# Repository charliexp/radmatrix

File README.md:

# radmatrix

Smol modular LED matrix, consisting of 3 types of 50x50mm modules:

- LED modules with a 20x20 matrix of 0603 red LEDs
- Driver modules at the end of rows and columns (bottom and right)
- Microcontroller (RP2040) board in the bottom-right corner

This was built as my first "serious" electronics project and its main purpose was to learn electronics a bit better. Some RP2040 embedded knowledge and a blinky lights object are nice side effects.

## Results

TODO: Photos, video, PCB renders

## Design details

The LED matrix and driver module PCB design were optimized for JLCPCB Assembly - i.e. only using parts available in its (LCSC) catalog and strongly preferring Basic parts to avoid paying feeder fees. The LEDs chosen were the cheapest available in JLC's catalog (they work fine btw).

The microcontroller board was optimized for JLC PCBA to a lesser extent -- I used multiple parts that would incur a feeder fee if not for the fact that I hand-soldered them.

The display is capable of:

- 8 bit red color
- 60fps (TODO, 30fps demonstrated)

Additionally, the MCU board can:

- Read multiple "videos" (specially encoded for this firmware) from an SD card
- Pipe in 8-bit 44kHz audio
- Transmit and receive CAN messages

## v2

Now that I've leraned from my mistakes, here's what I would do if I were to build a v2 of this display (I probably won't):

- Use square, preferably RGB LED "pixels"
- Fit them in a grid of **standard** spacing (i.e. 1, 1.27, 2, or 2.54mm)
- Put pixels edge to edge
  - Current design simplfiied connections and JLC assembly, but it's ugly
- Use a black PCB for the LED matrix for increased contrast
- Move driver modules from column/row ends to the backs of LED modules
  - The current design is kinda neat, but it doesn't scale, as with each additional row of modules, the perceptual brightness of LEDs goes down
- A 2mm-spacing 32x32 standard module seems reasonable
- Connection between LED module and driver module would be done by placing 1x16 SMD pin headers alongside corners (split in half, say, bottom-left and top-right for rows, and likewise for columns to allow edge-to-edge clearance)
  - Possibly some additional pin headers for added stability, maybe some solderable nuts - some mechanical connection between modules would be nice
- Driver modules
  - Would consider constant-current drivers, although resistor-based approach seems to work fine and appeared cheaper
  - If resistor-based approach is still used, I would consider a buck converter for creating a variable LED power supply
  - Would consider not skipping any of the shift register stages as that makes programming more annoying, and in this approach, it shouldn't make layout too difficult
  - Fix v1 bugs of course
  - Would consider faster shift registers. Perhaps 74HCT (5V supply to '595 gives best performance, and HCT can handle 3v3 input), or LV*
  - Would consider a decoder instead of shift registers for selecting rows. The current method is risky in that if programming is not done correctly, multiple LED rows could be lighting up at the same time (with one resistor for multiple LEDs), overstressing them. It's likely that current approach is cheaper and requires fewer signal lines though
- Driving the display
  - Each LED/driver module would have a separate connection to the MCU board - sharing row selection, OE, SRCLK, RCLK, lines, but each having its own SER line
  - With PIO, this would have minimal impact on driving performance, and RP2040 IO counts would likely allow for 16-20 module to be connected to a single MCU board
  - This could in principle be extended further with multiple MCU boards talking to a master
  - The display would become /32, so would be brighter and that would not depend on its height
  - Each driver module should have a buffer before/after it to improve the signal

Note that while most people do projects like this with an FPGA, in my opinion the RP2040, thanks to PIO, is more than capable enough for this job at a better price, and can do other stuff in addition to just driving the display. The main downside vs an FPGA is limited IO (30 pins), which limits how big of a display can be driven. With the design above, likely ~20kpx (though this could be optimized further)

Noting the above so I don't forget or in case someone else wants to take this project further. To me, this project has fulfilled its educational goal, and making large LED displays this way is impractical given that you can get HUB75 modules for less than just the LED cost off LCSC.

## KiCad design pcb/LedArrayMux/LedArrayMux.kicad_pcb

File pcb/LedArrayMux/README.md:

# LED Multiplexer

50x50mm module for driving rows and columns of LED Matrix modules

## Revisions

### Rev A

Manufactured 2024-04-06, delivered 2024-04-13.

Errata:

1. PMOS gates are pulled up to VLED (5V), while the shift register is powered from 3V3 and signals above VCC are not allowed. Ouch!
   - NMOS gates (i.e. row drivers) are not affected
   - This is not easily fixable on the board itself
   - It doesn't appear that 74HC595 dies immediately because of this, and the 10k resistor would limit worst-case scenario current to 0.5mA, but probably bad idea to ignore this altogether
   - It's possible to set VCC to 5V, and add level shifting on signal lines
   - Alternatively, the shift register could be replaced with 74HCT595 so that 3V3 signals register as logic high at 5V VCC

### Rev B

Ordered for manufacturing 2024-11-04 (est.), delivered TBD

Minor layout tweaks + added more decoupling capacitance. The major bugs are not fixed, as this rev is for a display that has it worked around.

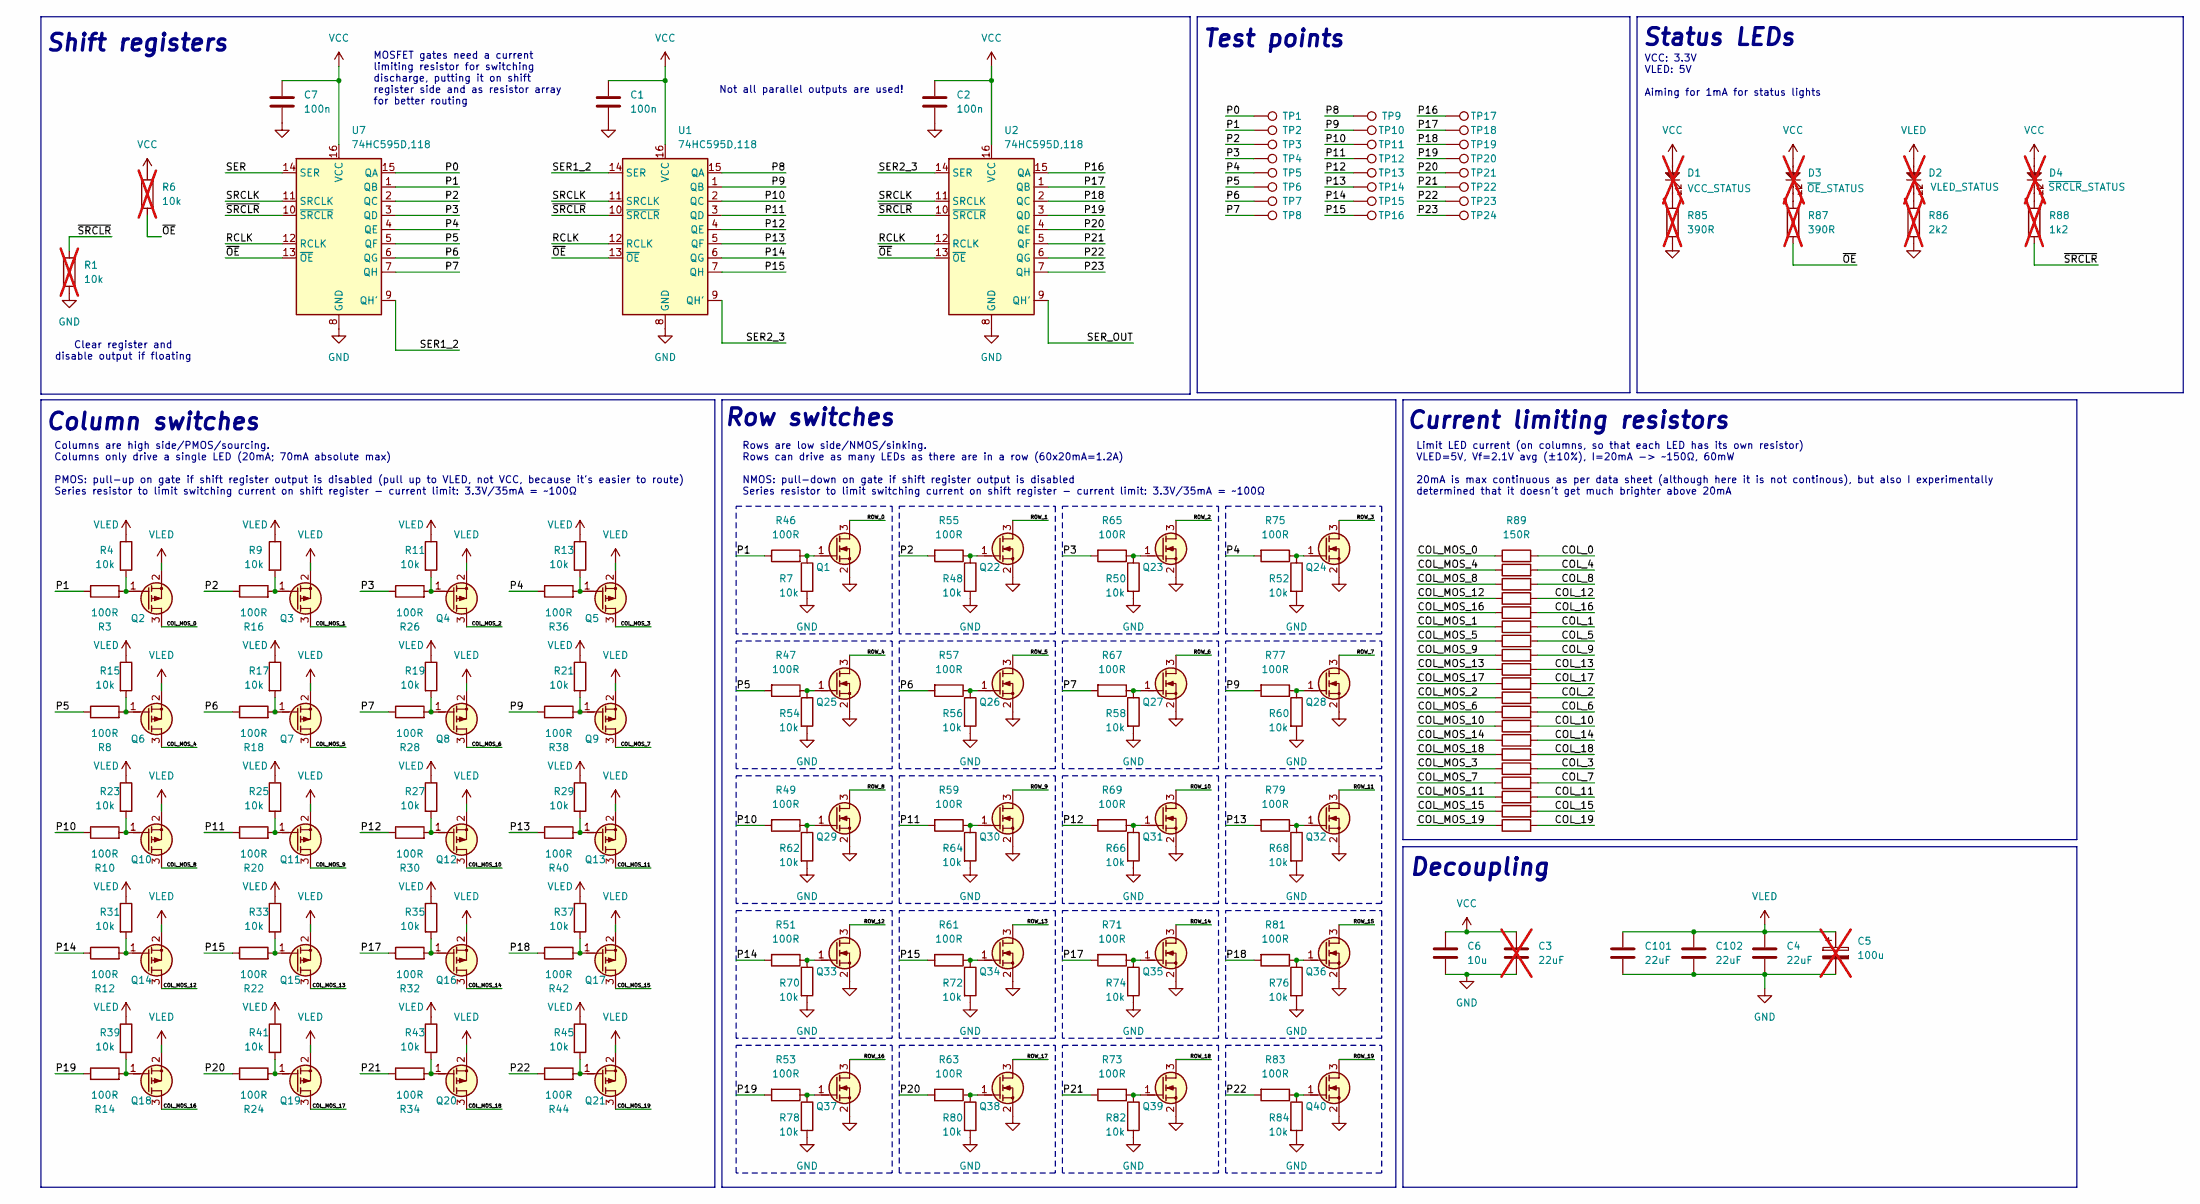
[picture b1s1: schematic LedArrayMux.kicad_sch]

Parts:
C1, C2, C7: 100n; R_0402_1005Metric; LCSC C307331
C3: 22uF; C_1206_3216Metric; LCSC C12891; not fitted
C4, C101, C102: 22uF; C_1206_3216Metric; LCSC C12891
C5: 100u; CP_EIA-3528-15_AVX-H; LCSC C16133; not fitted
C6: 10u; C_0603_1608Metric; LCSC C96446
D1, D2, D3: KT-0805G; LED_0805_2012Metric; LCSC C2297; not fitted
D4: KT-0805Y; LED_0805_2012Metric; LCSC C2296; not fitted
Q1, Q22, Q23, Q24, Q25, Q26, Q27, Q28, Q29, Q30, Q31, Q32, Q33, Q34, Q35, Q36, Q37, Q38, Q39, Q40: HL2304; SOT-23; LCSC C7420346
Q2, Q3, Q4, Q5, Q6, Q7, Q8, Q9, Q10, Q11, Q12, Q13, Q14, Q15, Q16, Q17, Q18, Q19, Q20, Q21: HL2301A; SOT-23; LCSC C7420344
R1, R6: 10k; R_0402_1005Metric; LCSC C25744; not fitted
R3, R8, R10, R12, R14, R16, R18, R20, R22, R24, R26, R28, R30, R32, R34, R36, R38, R40, R42, R44, R46, R47, R49, R51, R53, R55, R57, R59, R61, R63, R65, R67, R69, R71, R73, R75, R77, R79, R81, R83: 100R; R_0402_1005Metric
R4, R7, R9, R11, R13, R15, R17, R19, R21, R23, R25, R27, R29, R31, R33, R35, R37, R39, R41, R43, R45, R48, R50, R52, R54, R56, R58, R60, R62, R64, R66, R68, R70, R72, R74, R76, R78, R80, R82, R84: 10k; R_0402_1005Metric; LCSC C25744
R85, R87: 390R; R_0603_1608Metric; not fitted
R86: 2k2; R_0603_1608Metric; not fitted
R88: 1k2; R_0603_1608Metric; not fitted
R89, R90, R91, R92, R93, R94, R95, R96, R97, R98, R99, R100, R101, R102, R103, R104, R105, R106, R107, R108: 150R; R_0805_2012Metric
TP1, TP2, TP3, TP4, TP5, TP6, TP7, TP8, TP9, TP10, TP11, TP12, TP13, TP14, TP15, TP16, TP17, TP18, TP19, TP20, TP21, TP22, TP23, TP24: TestPoint; TestPoint_Pad_D1.0mm
U1, U2, U7: 74HC595D,118; SO-16_3.9x9.9mm_P1.27mm; LCSC C5947

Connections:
/COL_0: R89.2
/COL_1: R94.2
/COL_2: R99.2
/COL_3: R104.2
/COL_4: R90.2
/COL_5: R95.2
/COL_6: R100.2
/COL_7: R105.2
/COL_8: R91.2
/COL_9: R96.2
/COL_10: R101.2
/COL_11: R106.2
/COL_12: R92.2
/COL_13: R97.2
/COL_14: R102.2
/COL_15: R107.2
/COL_16: R93.2
/COL_17: R98.2
/COL_18: R103.2
/COL_19: R108.2
/COL_MOS_0: Q2.3 (D), R89.1
/COL_MOS_1: Q3.3 (D), R94.1
/COL_MOS_2: Q4.3 (D), R99.1
/COL_MOS_3: Q5.3 (D), R104.1
/COL_MOS_4: Q6.3 (D), R90.1
/COL_MOS_5: Q7.3 (D), R95.1
/COL_MOS_6: Q8.3 (D), R100.1
/COL_MOS_7: Q9.3 (D), R105.1
/COL_MOS_8: Q10.3 (D), R91.1
/COL_MOS_9: Q11.3 (D), R96.1
/COL_MOS_10: Q12.3 (D), R101.1
/COL_MOS_11: Q13.3 (D), R106.1
/COL_MOS_12: Q14.3 (D), R92.1
/COL_MOS_13: Q15.3 (D), R97.1
/COL_MOS_14: Q16.3 (D), R102.1
/COL_MOS_15: Q17.3 (D), R107.1
/COL_MOS_16: Q18.3 (D), R93.1
/COL_MOS_17: Q19.3 (D), R98.1
/COL_MOS_18: Q20.3 (D), R103.1
/COL_MOS_19: Q21.3 (D), R108.1
/P0: TP1.1, U7.15 (QA)
/P1: R3.1, R46.1, TP2.1, U7.1 (QB)
/P2: R16.1, R55.2, TP3.1, U7.2 (QC)
/P3: R26.1, R65.2, TP4.1, U7.3 (QD)
/P4: R36.1, R75.2, TP5.1, U7.4 (QE)
/P5: R8.1, R47.2, TP6.1, U7.5 (QF)
/P6: R18.1, R57.2, TP7.1, U7.6 (QG)
/P7: R28.1, R67.2, TP8.1, U7.7 (QH)
/P8: TP9.1, U1.15 (QA)
/P9: R38.1, R77.2, TP10.1, U1.1 (QB)
/P10: R10.1, R49.2, TP11.1, U1.2 (QC)
/P11: R20.1, R59.2, TP12.1, U1.3 (QD)
/P12: R30.1, R69.2, TP13.1, U1.4 (QE)
/P13: R40.1, R79.2, TP14.1, U1.5 (QF)
/P14: R12.1, R51.2, TP15.1, U1.6 (QG)
/P15: R22.1, R61.2, TP16.1, U1.7 (QH)
/P16: TP17.1, U2.15 (QA)
/P17: R32.1, R71.2, TP18.1, U2.1 (QB)
/P18: R42.1, R81.2, TP19.1, U2.2 (QC)
/P19: R14.1, R53.2, TP20.1, U2.3 (QD)
/P20: R24.1, R63.2, TP21.1, U2.4 (QE)
/P21: R34.1, R73.2, TP22.1, U2.5 (QF)
/P22: R44.1, R83.2, TP23.1, U2.6 (QG)
/P23: TP24.1, U2.7 (QH)
/RCLK: U1.12 (RCLK), U2.12 (RCLK), U7.12 (RCLK)
/ROW_0: Q1.3 (D)
/ROW_1: Q22.3 (D)
/ROW_2: Q23.3 (D)
/ROW_3: Q24.3 (D)
/ROW_4: Q25.3 (D)
/ROW_5: Q26.3 (D)
/ROW_6: Q27.3 (D)
/ROW_7: Q28.3 (D)
/ROW_8: Q29.3 (D)
/ROW_9: Q30.3 (D)
/ROW_10: Q31.3 (D)
/ROW_11: Q32.3 (D)
/ROW_12: Q33.3 (D)
/ROW_13: Q34.3 (D)
/ROW_14: Q35.3 (D)
/ROW_15: Q36.3 (D)
/ROW_16: Q37.3 (D)
/ROW_17: Q38.3 (D)
/ROW_18: Q39.3 (D)
/ROW_19: Q40.3 (D)
/SER: U7.14 (SER)
/SER1_2: U1.14 (SER), U7.9 (QH')
/SER2_3: U1.9 (QH'), U2.14 (SER)
/SER_OUT: U2.9 (QH')
/SRCLK: U1.11 (SRCLK), U2.11 (SRCLK), U7.11 (SRCLK)
/~OE: R6.2, R87.2, U1.13 (~OE), U2.13 (~OE), U7.13 (~OE)
/~SRCLR: R1.1, R88.2, U1.10 (~SRCLR), U2.10 (~SRCLR), U7.10 (~SRCLR)
GND: C1.2, C2.2, C3.2, C4.2, C5.2, C6.2, C7.2, C101.2, C102.2, Q1.2 (S), Q22.2 (S), Q23.2 (S), Q24.2 (S), Q25.2 (S), Q26.2 (S), Q27.2 (S), Q28.2 (S), Q29.2 (S), Q30.2 (S), Q31.2 (S), Q32.2 (S), Q33.2 (S), Q34.2 (S), Q35.2 (S), Q36.2 (S), Q37.2 (S), Q38.2 (S), Q39.2 (S), Q40.2 (S), R1.2, R7.2, R48.2, R50.2, R52.2, R54.2, R56.2, R58.2, R60.2, R62.2, R64.2, R66.2, R68.2, R70.2, R72.2, R74.2, R76.2, R78.2, R80.2, R82.2, R84.2, R85.2, R86.2, U1.8 (GND), U2.8 (GND), U7.8 (GND)
unnamed: D1.1, R85.1
unnamed: D2.1, R86.1
unnamed: D3.1, R87.1
unnamed: D4.1, R88.1
unnamed: Q1.1 (G), R7.1, R46.2
unnamed: Q2.1 (G), R3.2, R4.2
unnamed: Q3.1 (G), R9.2, R16.2
unnamed: Q4.1 (G), R11.2, R26.2
unnamed: Q5.1 (G), R13.2, R36.2
unnamed: Q6.1 (G), R8.2, R15.2
unnamed: Q7.1 (G), R17.2, R18.2
unnamed: Q8.1 (G), R19.2, R28.2
unnamed: Q9.1 (G), R21.2, R38.2
unnamed: Q10.1 (G), R10.2, R23.2
unnamed: Q11.1 (G), R20.2, R25.2
unnamed: Q12.1 (G), R27.2, R30.2
unnamed: Q13.1 (G), R29.2, R40.2
unnamed: Q14.1 (G), R12.2, R31.2
unnamed: Q15.1 (G), R22.2, R33.2
unnamed: Q16.1 (G), R32.2, R35.2
unnamed: Q17.1 (G), R37.2, R42.2
unnamed: Q18.1 (G), R14.2, R39.2
unnamed: Q19.1 (G), R24.2, R41.2
unnamed: Q20.1 (G), R34.2, R43.2
unnamed: Q21.1 (G), R44.2, R45.2
unnamed: Q22.1 (G), R48.1, R55.1
unnamed: Q23.1 (G), R50.1, R65.1
unnamed: Q24.1 (G), R52.1, R75.1
unnamed: Q25.1 (G), R47.1, R54.1
unnamed: Q26.1 (G), R56.1, R57.1
unnamed: Q27.1 (G), R58.1, R67.1
unnamed: Q28.1 (G), R60.1, R77.1
unnamed: Q29.1 (G), R49.1, R62.1
unnamed: Q30.1 (G), R59.1, R64.1
unnamed: Q31.1 (G), R66.1, R69.1
unnamed: Q32.1 (G), R68.1, R79.1
unnamed: Q33.1 (G), R51.1, R70.1
unnamed: Q34.1 (G), R61.1, R72.1
unnamed: Q35.1 (G), R71.1, R74.1
unnamed: Q36.1 (G), R76.1, R81.1
unnamed: Q37.1 (G), R53.1, R78.1
unnamed: Q38.1 (G), R63.1, R80.1
unnamed: Q39.1 (G), R73.1, R82.1
unnamed: Q40.1 (G), R83.1, R84.1
VCC: C1.1, C2.1, C3.1, C6.1, C7.1, D1.2, D3.2, D4.2, R6.1, U1.16 (VCC), U2.16 (VCC), U7.16 (VCC)
VLED: C4.1, C5.1, C101.1, C102.1, D2.2, Q2.2 (S), Q3.2 (S), Q4.2 (S), Q5.2 (S), Q6.2 (S), Q7.2 (S), Q8.2 (S), Q9.2 (S), Q10.2 (S), Q11.2 (S), Q12.2 (S), Q13.2 (S), Q14.2 (S), Q15.2 (S), Q16.2 (S), Q17.2 (S), Q18.2 (S), Q19.2 (S), Q20.2 (S), Q21.2 (S), R4.1, R9.1, R11.1, R13.1, R15.1, R17.1, R19.1, R21.1, R23.1, R25.1, R27.1, R29.1, R31.1, R33.1, R35.1, R37.1, R39.1, R41.1, R43.1, R45.1

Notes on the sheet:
Rows are low side/NMOS/sinking. Rows can drive as many LEDs as there are in a row (60x20mA=1.2A) NMOS: pull-down on gate if shift register output is disabled Series resistor to limit switching current on shift register - current limit: 3.3V/35mA = ~100Ω
Columns are high side/PMOS/sourcing. Columns only drive a single LED (20mA; 70mA absolute max) PMOS: pull-up on gate if shift register output is disabled (pull up to VLED, not VCC, because it's easier to route) Series resistor to limit switching current on shift register - current limit: 3.3V/35mA 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
Limit LED current (on columns, so that each LED has its own resistor) VLED=5V, Vf=2.1V avg (±10%), I=20mA -> ~150Ω, 60mW 20mA is max continuous as per data sheet (although here it is not continous), but also I experimentally determined that it doesn't get much brighter above 20mA
MOSFET gates need a current limiting resistor for switching discharge, putting it on shift register side and as resistor array for better routing
Not all parallel outputs are used!
Test points
Shift registers
Row switches
Status LEDs
Decoupling
VCC: 3.3V VLED: 5V Aiming for 1mA for status lights
Current limiting resistors
Column switches
Clear register and disable output if floating

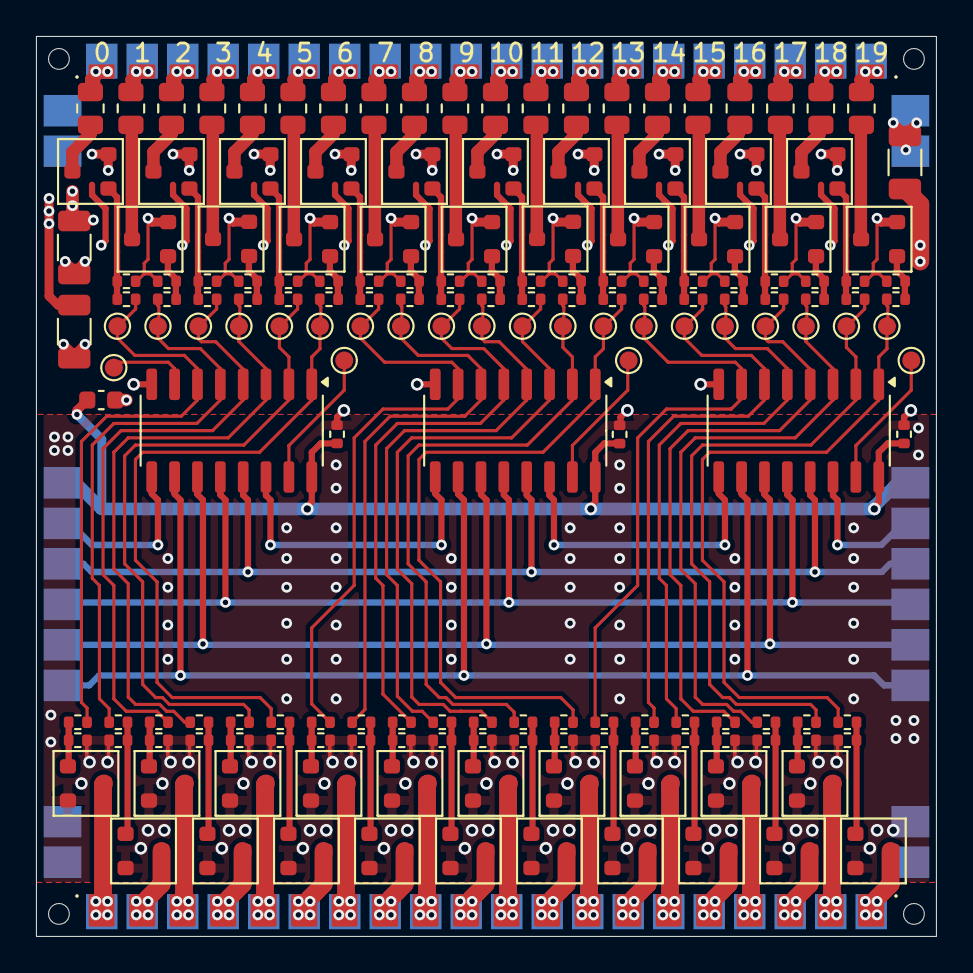
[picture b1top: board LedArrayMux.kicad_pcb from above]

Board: 2 copper layers, 50.0 x 50.0 mm, 174 parts (0 on the bottom side), 93 nets.

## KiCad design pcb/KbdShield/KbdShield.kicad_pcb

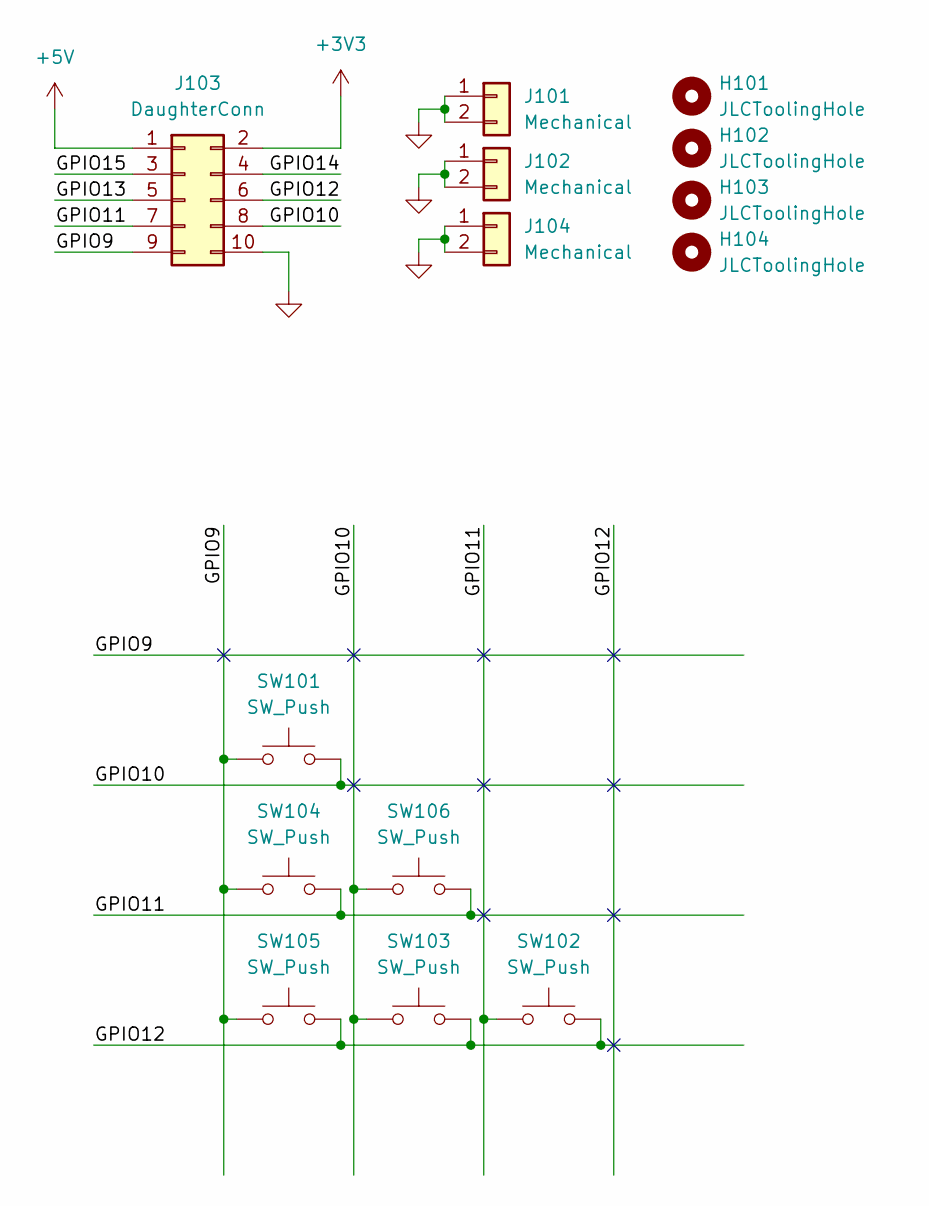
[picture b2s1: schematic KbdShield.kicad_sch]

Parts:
H101, H102, H103, H104: JLCToolingHole; jlcpcb-tooling-hole
J101, J102, J104: Mechanical; PinHeader_1x02_P2.54mm_Vertical
J103: DaughterConn; PinSocket_2x05_P2.54mm_Vertical
SW101, SW102, SW103, SW104, SW105, SW106: SW_Push; SW_Push_1P1T_NO_CK_KSC6xxJ

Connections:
+3V3: J103.2
+5V: J103.1
/GPIO9: J103.9, SW101.1, SW104.1, SW105.1
/GPIO10: J103.8, SW101.2, SW103.1, SW106.1
/GPIO11: J103.7, SW102.1, SW104.2, SW106.2
/GPIO12: J103.6, SW102.2, SW103.2, SW105.2
/GPIO13: J103.5
/GPIO14: J103.4
/GPIO15: J103.3
GND: J101.1, J101.2, J102.1, J102.2, J103.10, J104.1, J104.2

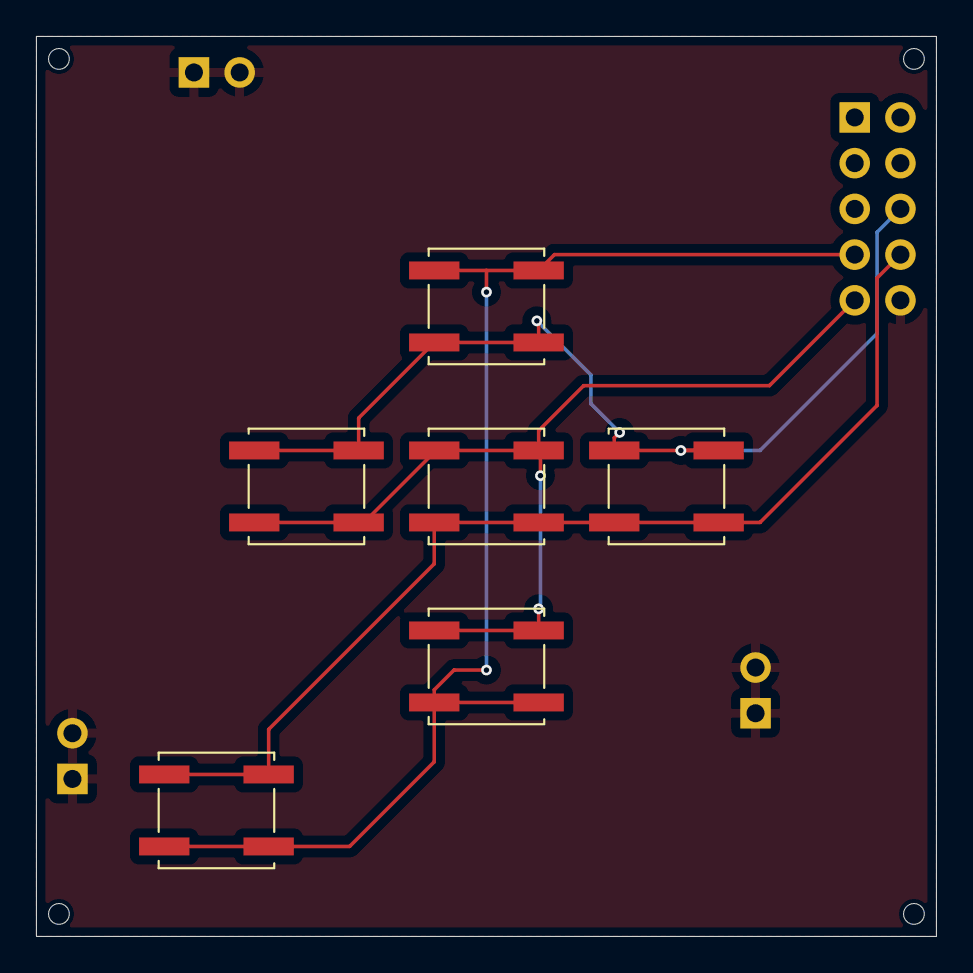
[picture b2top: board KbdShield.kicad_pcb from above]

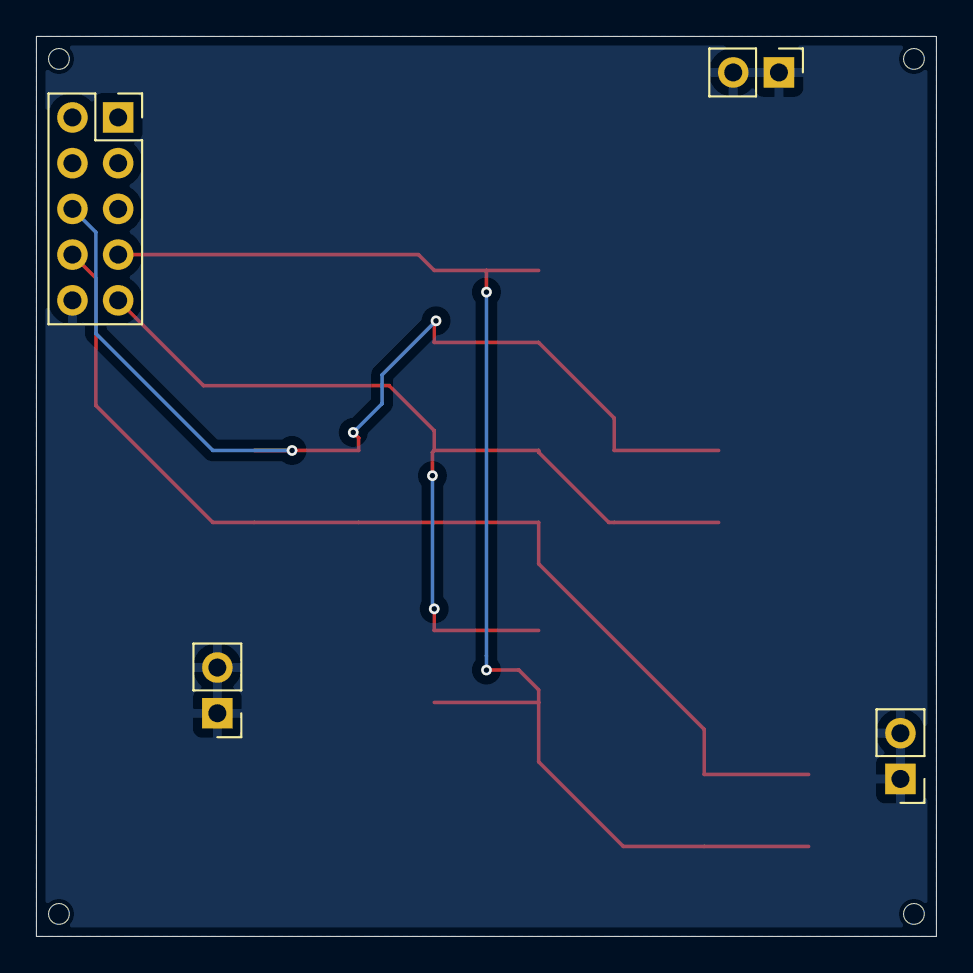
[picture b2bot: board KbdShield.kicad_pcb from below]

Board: 2 copper layers, 50.0 x 50.0 mm, 14 parts (4 on the bottom side), 5 nets.

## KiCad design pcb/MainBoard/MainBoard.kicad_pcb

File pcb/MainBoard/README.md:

# Main Board

50x50mm microcontroller module, driving LedArrayMux modules. Contains an RP2040 microcontroller, a CAN transceiver, PWM audio output, current sensing, and level shifters to work around LedArrayMux bugs.

## Revisions

### Rev A

Errata:

1. Level shifters are too slow to be useful
  - Workaround: decrease pullup values to obnoxiously low ones (100-180Ω); do not use level shifters; increase PIO delays until functional
2. CAN receive signal is not level shifted, which exposes RP2040 to a 5V signal
  - Workaround: Do nothing; replace with a 3v3 CAN transceiver
3. The 431 shunt voltage reference does not work correctly
  - Workaround: use main 3v3 regulator for vref
4. PWM audio signal filter is suspected to be responsible for poor quality audio

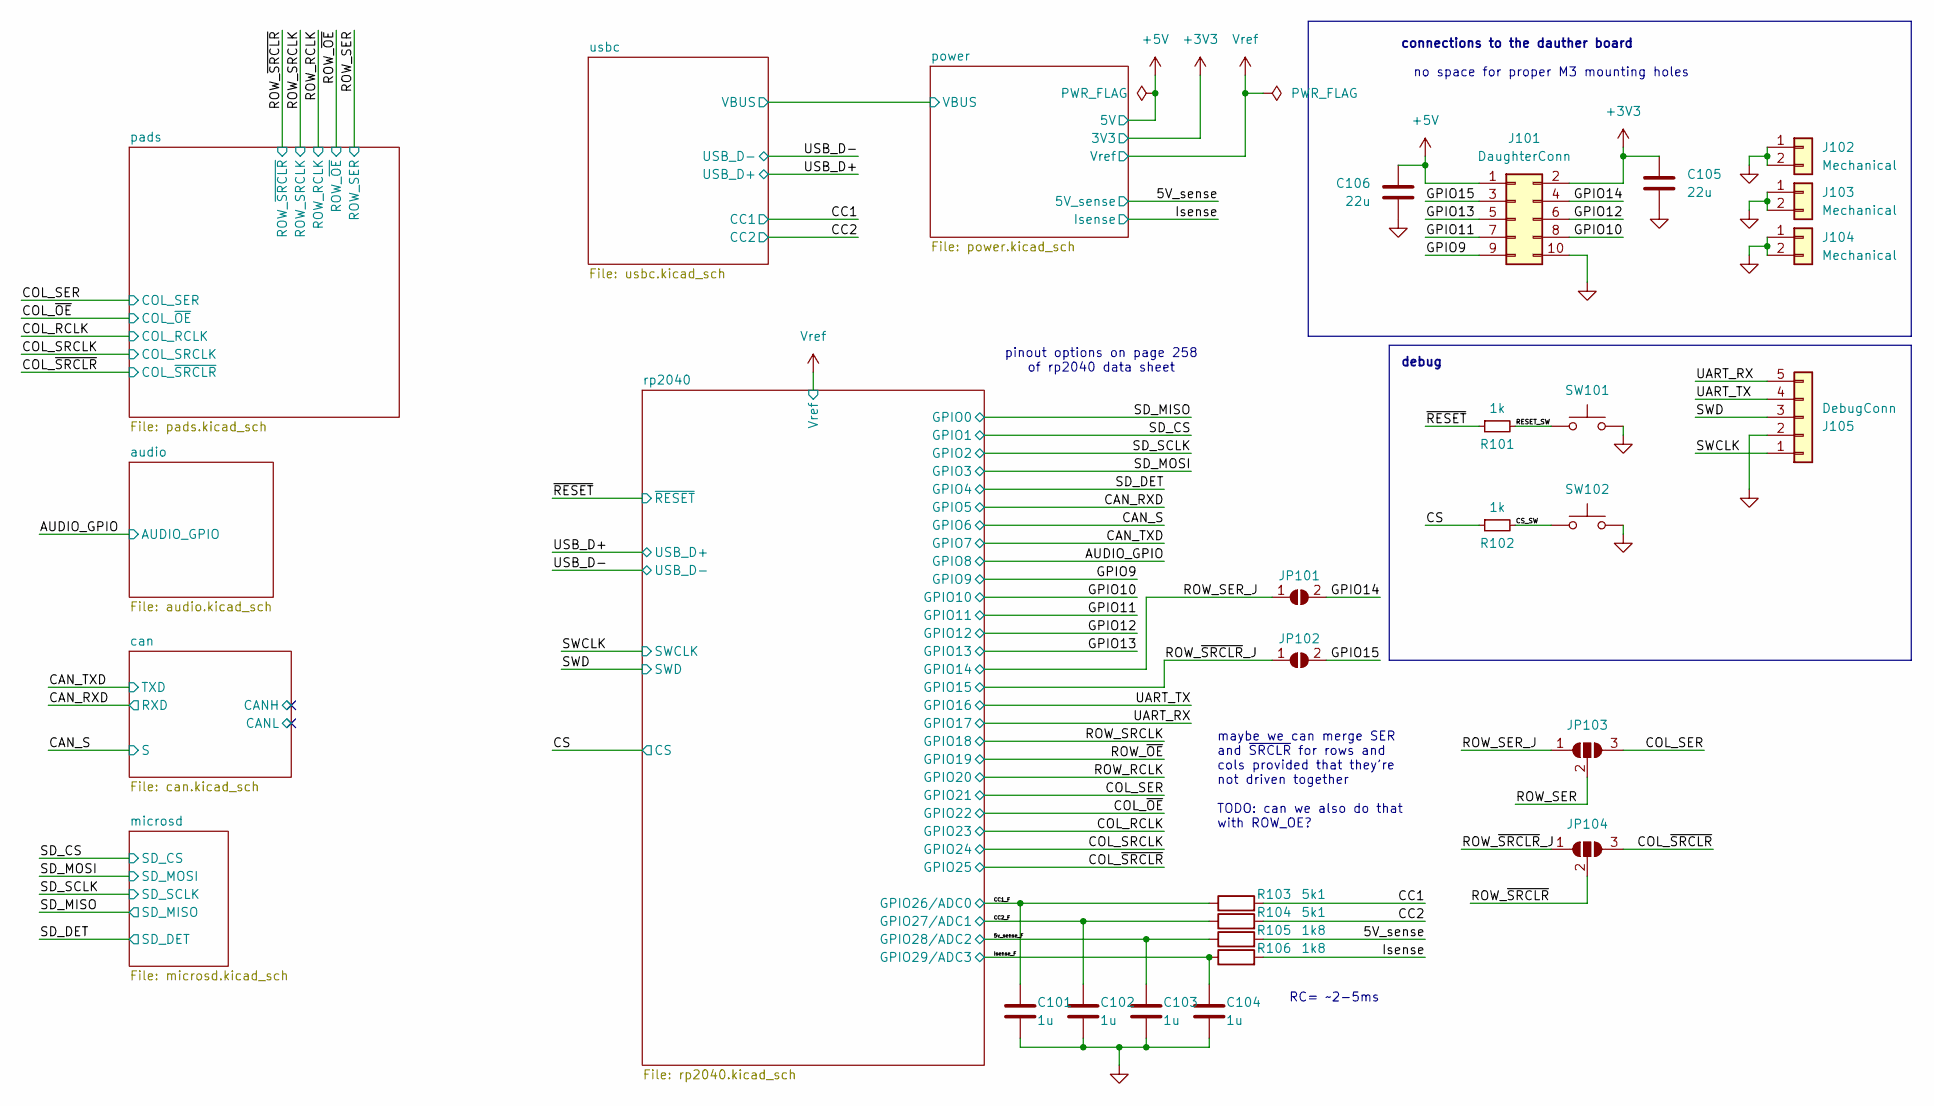
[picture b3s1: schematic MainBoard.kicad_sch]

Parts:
C101, C102, C103, C104: 1u; C_0402_1005Metric; LCSC C52923
C105, C106: 22u; C_0805_2012Metric; LCSC C45783
J101: DaughterConn; PinHeader_2x05_P2.54mm_Vertical
J102, J103, J104: Mechanical; PinHeader_1x02_P2.54mm_Vertical
J105: DebugConn; PinSocket_1x05_P2.54mm_Horizontal
JP101, JP102: SolderJumper_2_Open; SolderJumper-2_Open_RoundedPad_Smol
JP103, JP104: SolderJumper_3_Open; SolderJumper-3_Open_RoundedPad_Smol
R101, R102: 1k; R_0402_1005Metric; LCSC C11702
R103, R104: 5k1; R_0402_1005Metric; LCSC C25905
R105, R106: 1k8; R_0603_1608Metric; LCSC C4177
SW101, SW102: SW; HY-C-03

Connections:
+3V3: C105.1, J101.2; also elsewhere on the board
+5V: C106.1, J101.1; also elsewhere on the board
/5V_sense: R105.2; also elsewhere on the board
/5v_sense_F: C103.1, R105.1; also elsewhere on the board
/CC1: R103.2; also elsewhere on the board
/CC1_F: C101.1, R103.1; also elsewhere on the board
/CC2: R104.2; also elsewhere on the board
/CC2_F: C102.1, R104.1; also elsewhere on the board
/COL_SER: JP103.3 (B); also elsewhere on the board
/COL_~SRCLR: JP104.3 (B); also elsewhere on the board
/CS: R102.1; also elsewhere on the board
/CS_SW: R102.2, SW102.2
/GPIO9: J101.9; also elsewhere on the board
/GPIO10: J101.8; also elsewhere on the board
/GPIO11: J101.7; also elsewhere on the board
/GPIO12: J101.6; also elsewhere on the board
/GPIO13: J101.5; also elsewhere on the board
/GPIO14: J101.4, JP101.2 (B)
/GPIO15: J101.3, JP102.2 (B)
/Isense: R106.2; also elsewhere on the board
/Isense_F: C104.1, R106.1; also elsewhere on the board
/RESET_SW: R101.2, SW101.2
/ROW_SER: JP103.2 (C); also elsewhere on the board
/ROW_SER_J: JP101.1 (A), JP103.1 (A); also elsewhere on the board
/ROW_~SRCLR: JP104.2 (C); also elsewhere on the board
/ROW_~SRCLR_J: JP102.1 (A), JP104.1 (A); also elsewhere on the board
/SWCLK: J105.1; also elsewhere on the board
/SWD: J105.3; also elsewhere on the board
/UART_RX: J105.5; also elsewhere on the board
/UART_TX: J105.4; also elsewhere on the board
/~RESET: R101.1; also elsewhere on the board
GND: C101.2, C102.2, C103.2, C104.2, C105.2, C106.2, J101.10, J102.1, J102.2, J103.1, J103.2, J104.1, J104.2, J105.2, SW101.1, SW102.1; also elsewhere on the board

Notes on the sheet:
RC= ~2-5ms
maybe we can merge SER and ~{SRCLR} for rows and cols provided that they're not driven together TODO: can we also do that with ROW_OE?
pinout options on page 258 of rp2040 data sheet
connections to the dauther board
no space for proper M3 mounting holes
debug

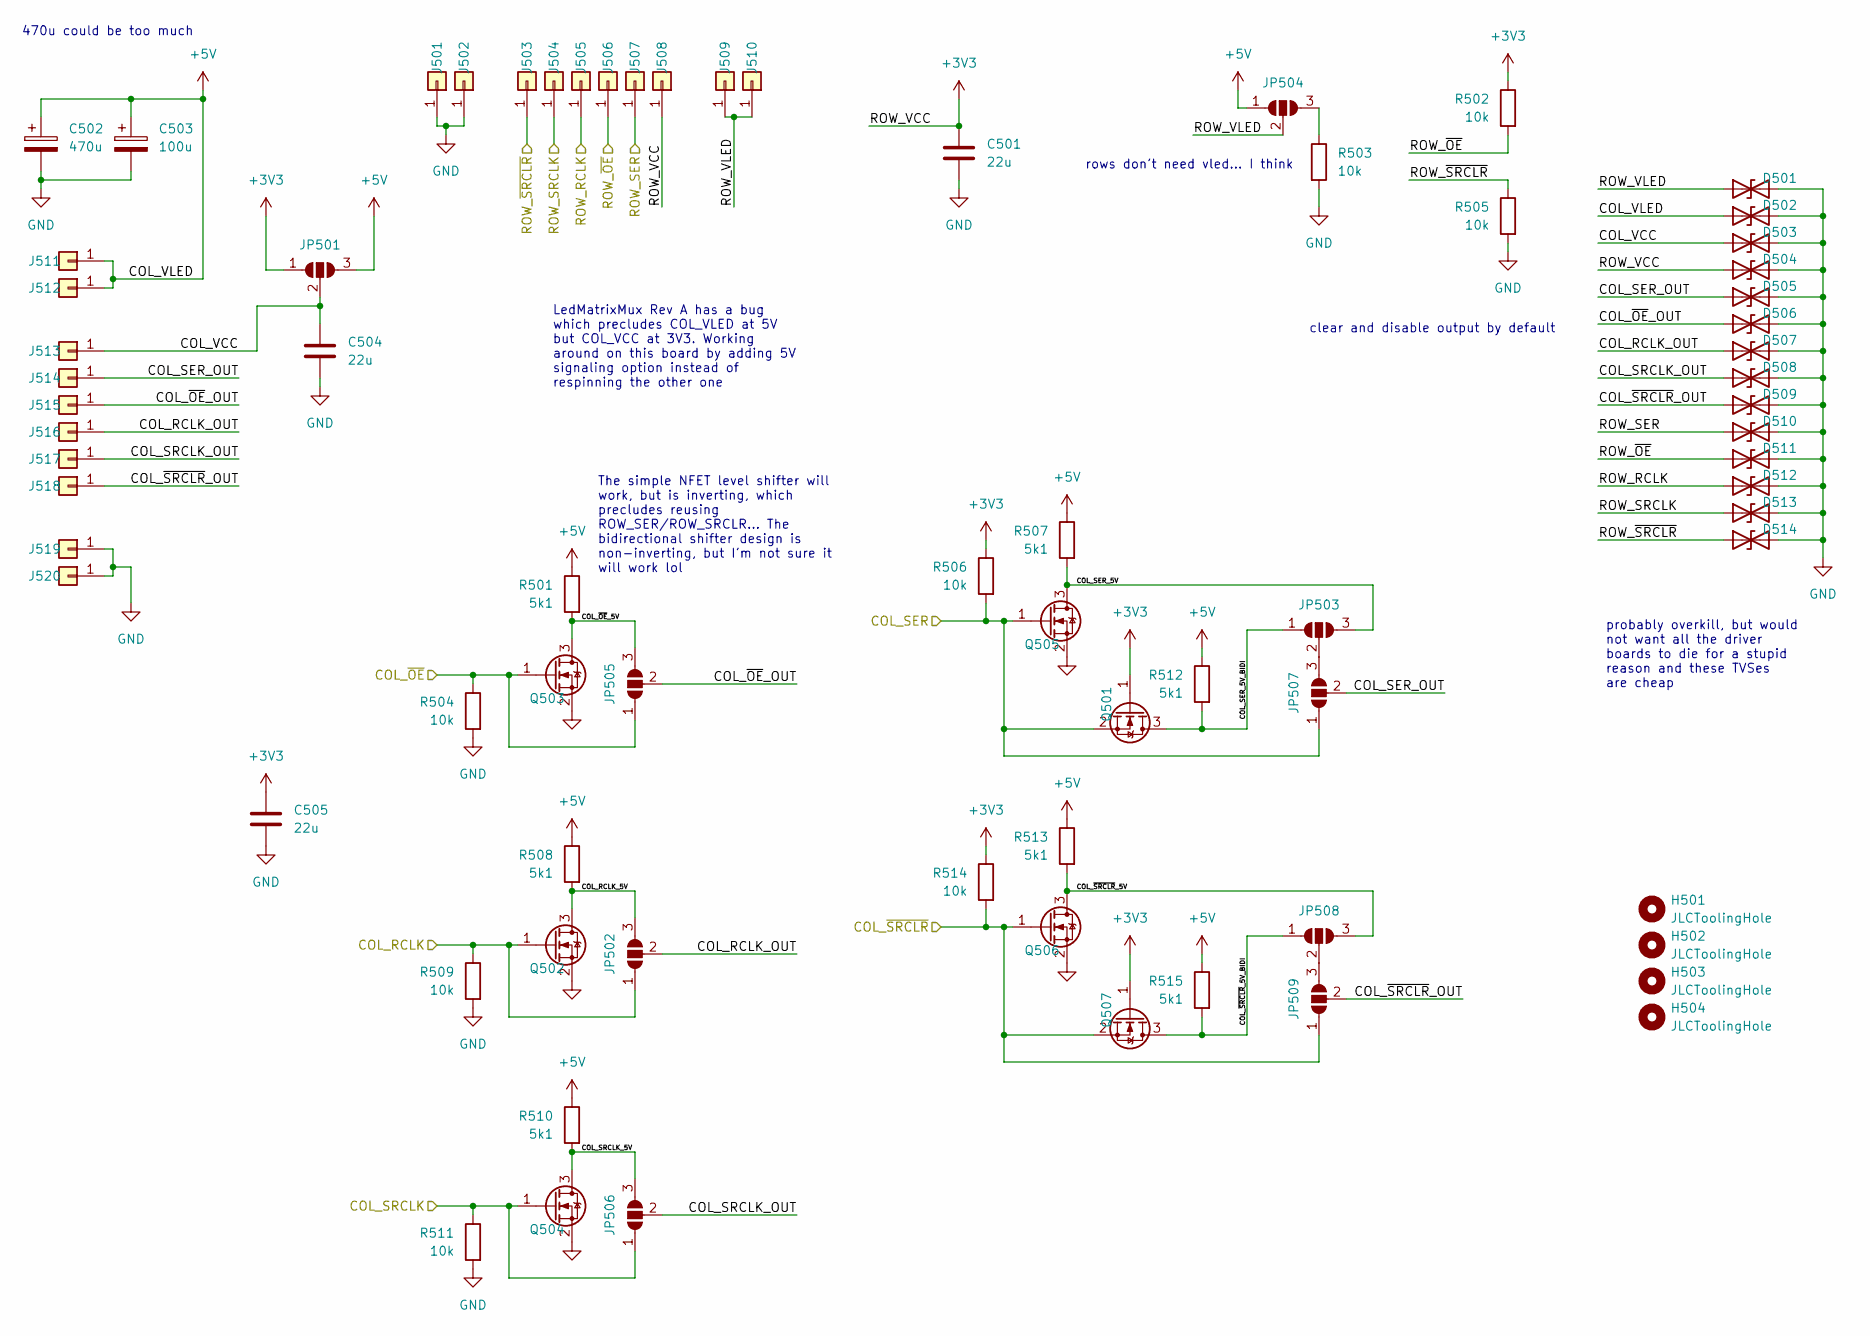
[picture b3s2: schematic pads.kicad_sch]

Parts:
C501, C504, C505: 22u; C_0805_2012Metric; LCSC C45783
C502: 470u; CP_Elec_8x10.5
C503: 100u; CP_EIA-3528-15_AVX-H; LCSC C16133
D501, D502, D503, D504, D505, D506, D507, D508, D509, D510, D511, D512, D513, D514: H5VL10B; DFN1006_TVS; LCSC C7420372
H501, H502, H503, H504: JLCToolingHole; jlcpcb-tooling-hole
J501, J502, J503, J504, J505, J506, J507, J508, J509, J510, J511, J512, J513, J514, J515, J516, J517, J518, J519, J520: Conn_01x01; solder-pad-2.25mm
JP501, JP502, JP503, JP504, JP505, JP506, JP507, JP508, JP509: SolderJumper_3_Open; SolderJumper-3_Open_RoundedPad_Smol
Q501, Q502, Q503, Q504, Q505, Q506, Q507: HL2304; SOT-23; LCSC C7420346
R501, R507, R508, R510, R512, R513, R515: 5k1; R_0402_1005Metric; LCSC C25905
R502, R503, R504, R505, R506, R509, R511, R514: 10k; R_0402_1005Metric; LCSC C25744

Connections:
+3V3: C501.1, C505.1, D504.1 (A1), J508.1, JP501.1 (A), Q501.1 (G), Q507.1 (G), R502.1, R506.1, R514.1; also elsewhere on the board
+5V: C502.1, C503.1, D502.1 (A1), J511.1, J512.1, JP501.3 (B), JP504.1 (A), R501.1, R507.1, R508.1, R510.1, R512.1, R513.1, R515.1; also elsewhere on the board
/COL_RCLK: JP502.1 (A), Q502.1 (G), R509.1; also elsewhere on the board
/COL_SER: JP507.1 (A), Q501.2 (S), Q505.1 (G), R506.2; also elsewhere on the board
/COL_SRCLK: JP506.1 (A), Q504.1 (G), R511.1; also elsewhere on the board
/COL_~OE: JP505.1 (A), Q503.1 (G), R504.1; also elsewhere on the board
/COL_~SRCLR: JP509.1 (A), Q506.1 (G), Q507.2 (S), R514.2; also elsewhere on the board
/ROW_RCLK: D512.1 (A1), J505.1; also elsewhere on the board
/ROW_SER: D510.1 (A1), J507.1; also elsewhere on the board
/ROW_SRCLK: D513.1 (A1), J504.1; also elsewhere on the board
/ROW_~OE: D511.1 (A1), J506.1, R502.2; also elsewhere on the board
/ROW_~SRCLR: D514.1 (A1), J503.1, R505.1; also elsewhere on the board
/pads/COL_RCLK_5V: JP502.3 (B), Q502.3 (D), R508.2
/pads/COL_RCLK_OUT: D507.1 (A1), J516.1, JP502.2 (C)
/pads/COL_SER_5V: JP503.3 (B), Q505.3 (D), R507.2
/pads/COL_SER_5V_BIDI: JP503.1 (A), Q501.3 (D), R512.2
/pads/COL_SER_OUT: D505.1 (A1), J514.1, JP507.2 (C)
/pads/COL_SRCLK_5V: JP506.3 (B), Q504.3 (D), R510.2
/pads/COL_SRCLK_OUT: D508.1 (A1), J517.1, JP506.2 (C)
/pads/COL_VCC: C504.1, D503.1 (A1), J513.1, JP501.2 (C)
/pads/COL_~OE_5V: JP505.3 (B), Q503.3 (D), R501.2
/pads/COL_~OE_OUT: D506.1 (A1), J515.1, JP505.2 (C)
/pads/COL_~SRCLR_5V: JP508.3 (B), Q506.3 (D), R513.2
/pads/COL_~SRCLR_5V_BIDI: JP508.1 (A), Q507.3 (D), R515.2
/pads/COL_~SRCLR_OUT: D509.1 (A1), J518.1, JP509.2 (C)
/pads/ROW_VLED: D501.1 (A1), J509.1, J510.1, JP504.2 (C)
GND: C501.2, C502.2, C503.2, C504.2, C505.2, D501.2 (A2), D502.2 (A2), D503.2 (A2), D504.2 (A2), D505.2 (A2), D506.2 (A2), D507.2 (A2), D508.2 (A2), D509.2 (A2), D510.2 (A2), D511.2 (A2), D512.2 (A2), D513.2 (A2), D514.2 (A2), J501.1, J502.1, J519.1, J520.1, Q502.2 (S), Q503.2 (S), Q504.2 (S), Q505.2 (S), Q506.2 (S), R503.2, R504.2, R505.2, R509.2, R511.2; also elsewhere on the board
unnamed: JP503.2 (C), JP507.3 (B)
unnamed: JP504.3 (B), R503.1
unnamed: JP508.2 (C), JP509.3 (B)

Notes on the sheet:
The simple NFET level shifter will work, but is inverting, which precludes reusing ROW_SER/ROW_SRCLR… The bidirectional shifter design is non-inverting, but I'm not sure it will work lol
probably overkill, but would not want all the driver boards to die for a stupid reason and these TVSes are cheap
LedMatrixMux Rev A has a bug which precludes COL_VLED at 5V but COL_VCC at 3V3. Working around on this board by adding 5V signaling option instead of respinning the other one
470u could be too much
clear and disable output by default
rows don't need vled… I think

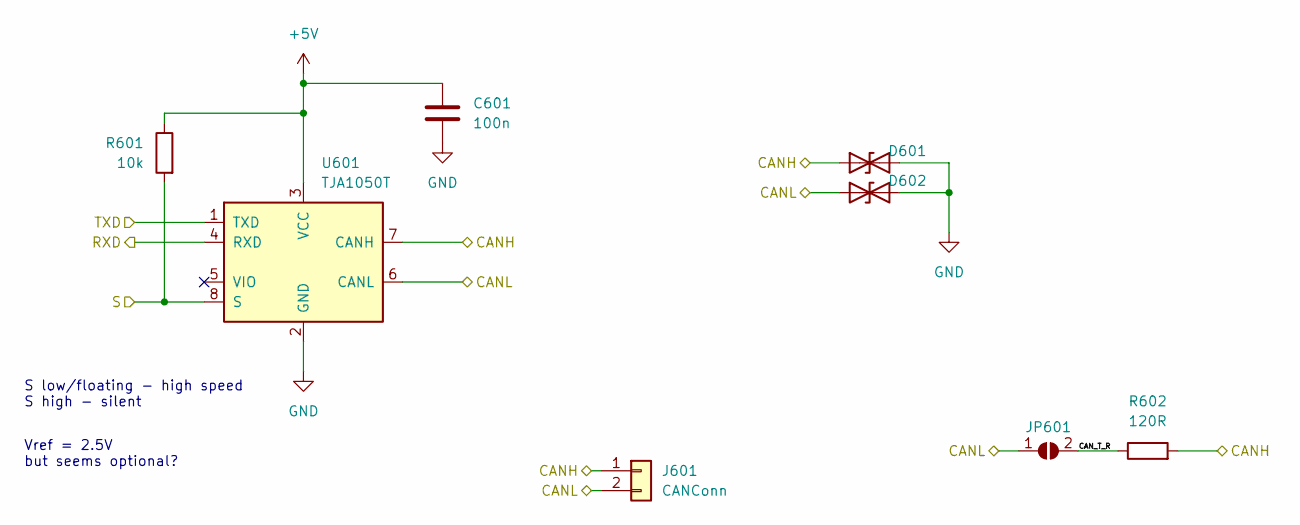
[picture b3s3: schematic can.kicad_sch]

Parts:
C601: 100n; C_0402_1005Metric; LCSC C1525
D601, D602: H5VL10B; DFN1006_TVS; LCSC C7420372
J601: CANConn; PinHeader_1x02_P2.54mm_Horizontal
JP601: SolderJumper_2_Open; SolderJumper-2_Open_RoundedPad_Smol
R601: 10k; R_0402_1005Metric; LCSC C25744
R602: 120R; R_0402_1005Metric; LCSC C25079
U601: TJA1050T; SOIC-8_3.9x4.9mm_P1.27mm; LCSC C6952

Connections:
+5V: C601.1, R601.1, U601.3 (VCC); also elsewhere on the board
/CAN_RXD: U601.4 (RXD); also elsewhere on the board
/CAN_S: R601.2, U601.8 (S); also elsewhere on the board
/CAN_TXD: U601.1 (TXD); also elsewhere on the board
/can/CANH: D601.1 (A1), J601.1, R602.2, U601.7 (CANH)
/can/CANL: D602.1 (A1), J601.2, JP601.1 (A), U601.6 (CANL)
/can/CAN_T_R: JP601.2 (B), R602.1
GND: C601.2, D601.2 (A2), D602.2 (A2), U601.2 (GND); also elsewhere on the board

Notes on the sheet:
S low/floating - high speed S high - silent
Vref = 2.5V but seems optional?
